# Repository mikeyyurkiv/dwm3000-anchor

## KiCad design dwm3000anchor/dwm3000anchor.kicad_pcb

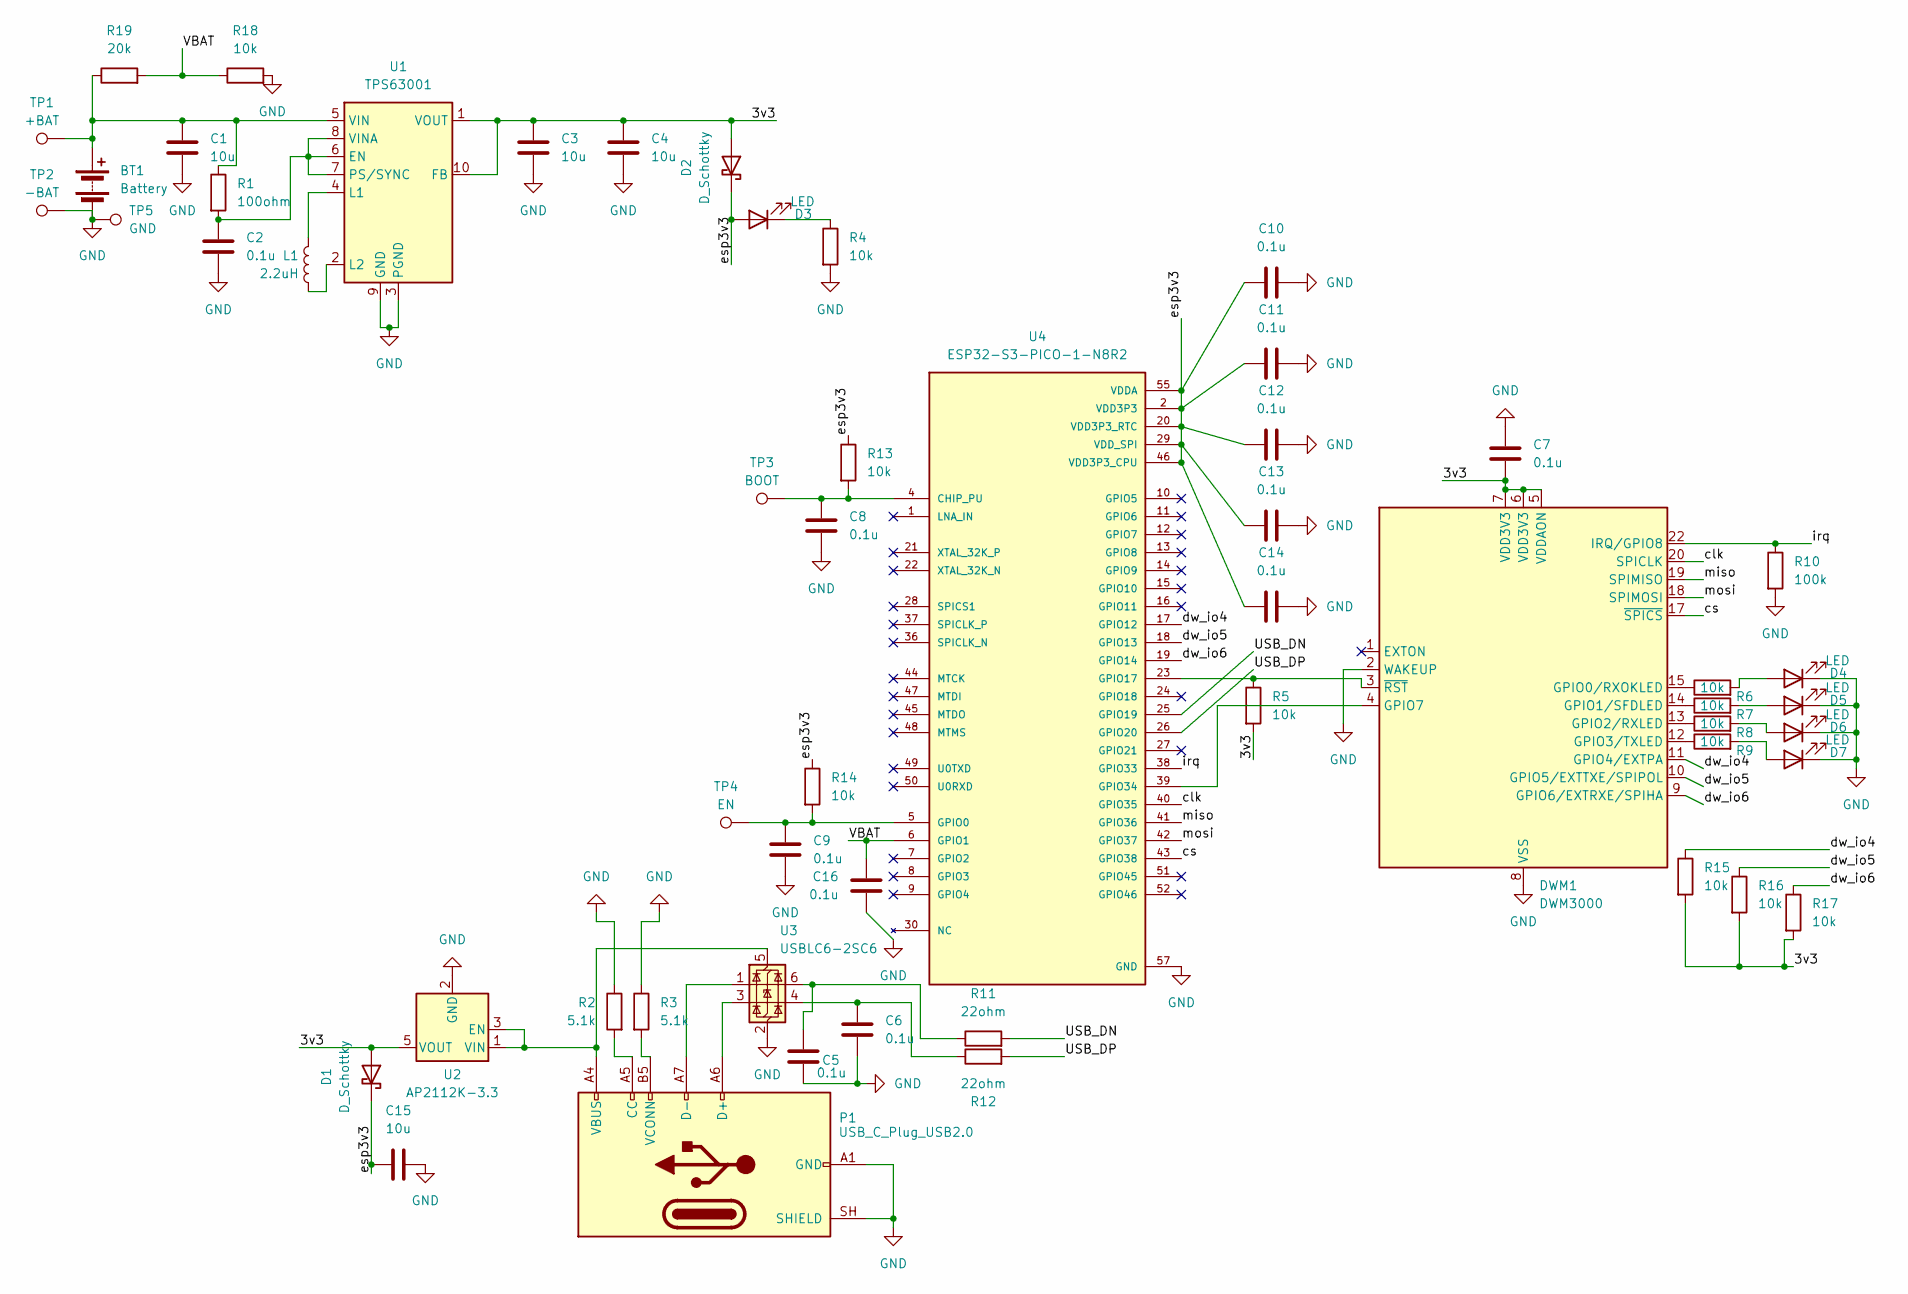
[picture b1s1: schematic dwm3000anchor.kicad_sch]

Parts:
BT1: Battery; TestPoint_Pad_2.0x2.0mm
C1, C3, C4, C15: 10u; C_0603_1608Metric_Pad1.08x0.95mm_HandSolder
C2, C5, C6, C7, C8, C9, C10, C11, C12, C13, C14, C16: 0.1u; C_0603_1608Metric_Pad1.08x0.95mm_HandSolder
D1, D2: D_Schottky; D_SOD-323
D3, D4, D5, D6, D7: LED; LED_0603_1608Metric
DWM1: DWM3000; DWM1000
L1: 2.2uH; L_Changjiang_FNR4012S
P1: USB_C_Plug_USB2.0; USB_C_Receptacle_GCT_USB4105-xx-A_16P_TopMnt_Horizontal
R1: 100ohm; R_0603_1608Metric_Pad0.98x0.95mm_HandSolder
R2, R3: 5.1k; R_0603_1608Metric_Pad0.98x0.95mm_HandSolder
R4, R5, R6, R7, R8, R9, R13, R14, R15, R16, R17, R18: 10k; R_0603_1608Metric_Pad0.98x0.95mm_HandSolder
R10: 100k; R_0603_1608Metric_Pad0.98x0.95mm_HandSolder
R11, R12: 22ohm; R_0603_1608Metric_Pad0.98x0.95mm_HandSolder
R19: 20k; R_0603_1608Metric_Pad0.98x0.95mm_HandSolder
TP1: +BAT; TestPoint_THTPad_D1.5mm_Drill0.7mm
TP2: -BAT; TestPoint_THTPad_1.5x1.5mm_Drill0.7mm
TP3: BOOT; TestPoint_Pad_D2.0mm
TP4: EN; TestPoint_Pad_D2.0mm
TP5: GND; TestPoint_Pad_D2.0mm
U1: TPS63001; Texas_DRC0010J_ThermalVias
U2: AP2112K-3.3; SOT-23-5
U3: USBLC6-2SC6; SOT-23-6
U4: ESP32-S3-PICO-1-N8R2; esp32-s3-pico-n8r2; PARTREV 1.0

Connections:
/3v3: C3.1, C4.1, C7.2, D1.2 (A), D2.2 (A), DWM1.5 (VDDAON), DWM1.6 (VDD3V3), DWM1.7 (VDD3V3), R5.2, R15.2, R16.2, R17.2, U1.1 (VOUT), U1.10 (FB), U2.5 (VOUT)
/USB_DN: R11.2, U4.25 (GPIO19)
/USB_DP: R12.2, U4.26 (GPIO20)
/VBAT: C16.1, R18.1, R19.2, U4.6 (GPIO1)
/clk: DWM1.20 (SPICLK), U4.40 (GPIO35)
/cs: DWM1.17 (~SPICS), U4.43 (GPIO38)
/dw_io4: DWM1.11 (GPIO4/EXTPA), R15.1, U4.17 (GPIO12)
/dw_io5: DWM1.10 (GPIO5/EXTTXE/SPIPOL), R16.1, U4.18 (GPIO13)
/dw_io6: DWM1.9 (GPIO6/EXTRXE/SPIHA), R17.1, U4.19 (GPIO14)
/irq: DWM1.22 (IRQ/GPIO8), R10.1, U4.38 (GPIO33)
/miso: DWM1.19 (SPIMISO), U4.41 (GPIO36)
/mosi: DWM1.18 (SPIMOSI), U4.42 (GPIO37)
GND: BT1.2 (-), C1.2, C2.2, C3.2, C4.2, C5.2, C6.2, C7.1, C8.2, C9.2, C10.1, C11.2, C12.2, C13.2, C14.2, C15.2, C16.2, D4.1 (K), D5.1 (K), D6.1 (K), D7.1 (K), DWM1.2 (WAKEUP), DWM1.8 (VSS), DWM1.16 (VSS), DWM1.21 (VSS), DWM1.23 (VSS), DWM1.24 (VSS), P1.A1 (GND), P1.A12 (GND), P1.B1 (GND), P1.B12 (GND), P1.SH (SHIELD), R2.1, R3.1, R4.2, R10.2, R18.2, TP2.1 (1_1), TP5.1 (1_1), U1.3 (PGND), U1.9 (GND), U1.11 (PGND), U2.2 (GND), U3.2 (GND), U4.57 (GND)
unnamed: BT1.1 (+), C1.1, R1.1, R19.1, TP1.1 (1_1), U1.5 (VIN)
unnamed: C5.1, R11.1, U3.6 (I/O1)
unnamed: C6.1, R12.1, U3.4 (I/O2)
unnamed: D3.1 (K), R4.1
unnamed: D4.2 (A), R6.2
unnamed: D5.2 (A), R7.2
unnamed: D6.2 (A), R8.2
unnamed: D7.2 (A), R9.2
unnamed: DWM1.15 (GPIO0/RXOKLED), R6.1
unnamed: DWM1.14 (GPIO1/SFDLED), R7.1
unnamed: DWM1.13 (GPIO2/RXLED), R8.1
unnamed: DWM1.12 (GPIO3/TXLED), R9.1
unnamed: DWM1.4 (GPIO7), U4.39 (GPIO34)
unnamed: DWM1.3 (~RST), R5.1, U4.23 (GPIO17)
unnamed: P1.A5 (CC), R2.2
unnamed: P1.A6 (D+), U3.3 (I/O2)
unnamed: P1.A7 (D-), U3.1 (I/O1)
unnamed: P1.B5 (VCONN), R3.2
unnamed: C2.1, R1.2, U1.6 (EN), U1.7 (PS/SYNC), U1.8 (VINA)
unnamed: L1.1, U1.4 (L1)
unnamed: L1.2, U1.2 (L2)
unnamed: P1.A4 (VBUS), P1.A9 (VBUS), P1.B4 (VBUS), P1.B9 (VBUS), U2.1 (VIN), U2.3 (EN), U3.5 (VBUS)
unnamed: C8.1, R13.2, TP3.1 (1_1), U4.4 (CHIP_PU)
unnamed: C9.1, R14.2, TP4.1 (1_1), U4.5 (GPIO0)
VDD3P3: C10.2, C11.1, C12.1, C13.1, C14.1, C15.1, D1.1 (K), D2.1 (K), D3.2 (A), R13.1, R14.1, U4.2 (VDD3P3), U4.3 (VDD3P3), U4.20 (VDD3P3_RTC), U4.29 (VDD_SPI), U4.46 (VDD3P3_CPU), U4.55 (VDDA), U4.56 (VDDA)

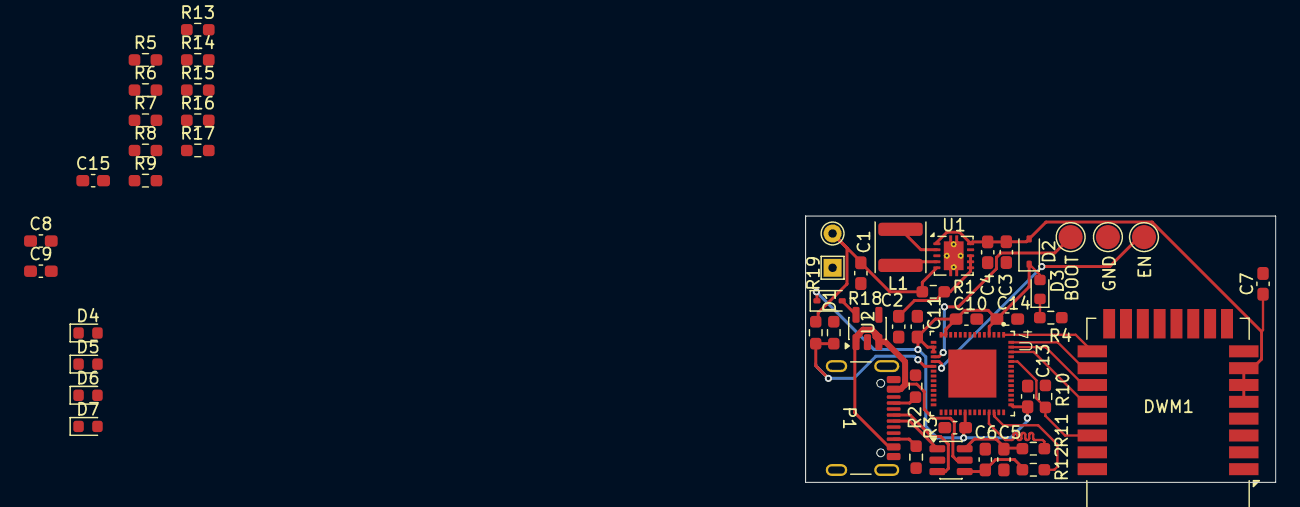
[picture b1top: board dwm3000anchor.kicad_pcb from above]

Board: 4 copper layers, 39.1 x 22.1 mm, 54 parts (1 on the bottom side), 38 nets.
